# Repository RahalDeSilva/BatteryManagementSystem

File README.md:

# BatteryManagementSystem
EKF-based State of Charge estimator for Li-ion cells using NASA battery dataset

> ⚠️ Active development — ongoing BMS prototype. Expect breaking changes between commits.

A MATLAB-based Battery Management System (BMS) prototype focused on State of Charge (SOC) estimation for lithium-ion cells. Currently implements an Extended Kalman Filter (EKF) with a first-order RC equivalent circuit model, validated against a parallel Coulomb Counting benchmark using the NASA battery dataset.

---

## Current Status

| Module | Status |
|---|---|
| EKF SOC Estimator | ✅ In progress |
| Coulomb Counting benchmark | ✅ In progress |
| OCV–SOC lookup table | ✅ In progress |
| Cell balancing | 🔲 Planned |
| Thermal modelling | 🔲 Planned |
| State of Health (SOH) | 🔲 Planned |
| Embedded deployment | 🔲 Planned |

## Status (as of this checkpoint)
- ✅ EKF SOC estimation working on NASA 00001.csv (single discharge cycle)
- ✅ Variable timestep handling (9.4-13.9s)
- ✅ Current sign convention corrected (NASA: discharge = negative)
- ✅ Nonlinear OCV lookup table (extended range + densified knee region)
- 📊 Operational Voltage RMSE: 0.061 V (excludes end-of-discharge relaxation)
- 📌 Known limitation: residual spikes during end-of-discharge relaxation
  (1st-order RC model limitation — see Future Work)
- 📌 EKF vs Coulomb Counting gap (~3.4pp) likely due to placeholder
  capacity Q=2.0Ah vs actual aged-cell capacity — candidate for SOH module

---

## Battery Model

First-order RC equivalent circuit.

**State vector:** `x = [SOC, Vrc]`

**State equations:**

```
SOC(k+1) = SOC(k) − I·dt / Q
Vrc(k+1) = α·Vrc(k) + β·I

α = exp(−dt / (R1·C1))
β = R1·(1 − α)
```

**Terminal voltage measurement equation:**

```
V = OCV(SOC) − I·R0 − Vrc
```

---

## Repository Structure

```
BatteryManagementSystem/
├── SOC_Estimation/
    ├── data/
│       └── 00001.csv         % NASA Li-ion discharge dataset
│   ├── main.m            % EKF loop + Coulomb counting + plots
│   ├── battery_step.m    % RC circuit state transition function
│   ├── ekf_step.m        % EKF predict and update step
│   ├── ocv.m             % Nonlinear OCV piecewise-linear lookup
│   └── load_data.m       % NASA dataset loader
└── README.md
```

---

## Requirements

- MATLAB R2020a or later
- No additional toolboxes required for current modules

---

## Dataset

NASA battery discharge dataset (00001.csv).
Columns: `Voltage_measured`, `Current_measured`, `Temperature_measured`, `Current_load`, `Voltage_load`, `Time`

> Note: NASA dataset uses a non-standard current sign convention. Discharge current is negated in `load_data.m` before processing.

---

## EKF Tuning Parameters

| Parameter | Value | Description |
|---|---|---|
| Q | 2.0 Ah | Nominal cell capacity |
| R0 | ~0.05 Ω | Series resistance |
| R1 | ~0.02 Ω | RC branch resistance |
| C1 | ~2000 F | RC branch capacitance |
| Qk(1,1) | 1e-7 | Process noise — SOC |
| Qk(2,2) | 1e-5 | Process noise — Vrc |
| Rk | 4e-4 | Measurement noise (0.02V std) |

---

## References

- Gregory Plett, *Algorithms for Battery Management Systems* — Coursera
- NASA Prognostics Center of Excellence Battery Dataset
- Plett, G.L., *Battery Management Systems, Vol. 1: Battery Modeling*

---

## License

MIT License — see `LICENSE` for details.

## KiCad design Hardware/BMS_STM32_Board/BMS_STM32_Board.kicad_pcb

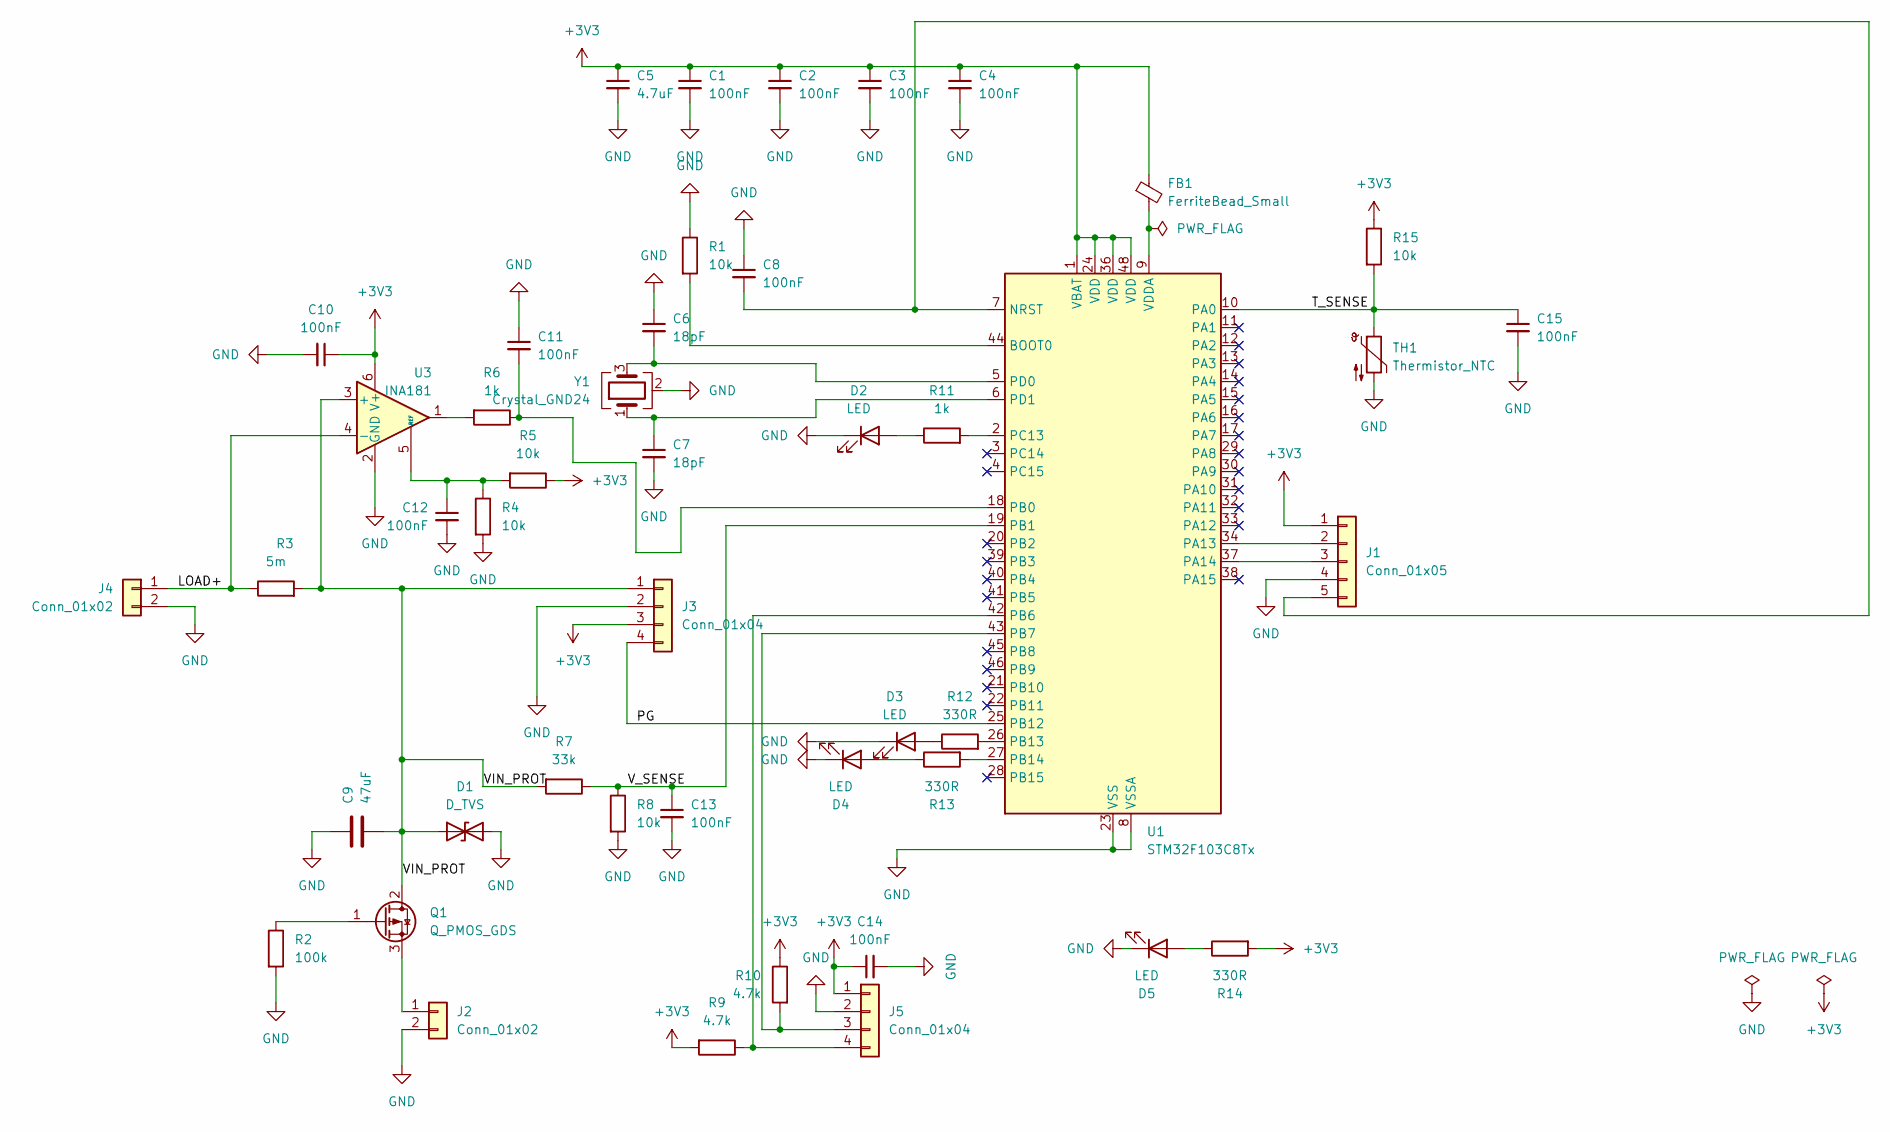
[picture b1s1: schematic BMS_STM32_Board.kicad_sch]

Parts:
C1, C2, C3, C4, C8, C10, C11, C12, C13, C14, C15: 100nF; C_0603_1608Metric
C5: 4.7uF; C_0805_2012Metric
C6, C7: 18pF; C_0603_1608Metric
C9: 47uF; CP_Radial_D6.3mm_P2.50mm
D1: D_TVS; D_SMA
D2, D3, D4, D5: LED; LED_0805_2012Metric
FB1: FerriteBead_Small; L_0603_1608Metric
J1: Conn_01x05; PinHeader_1x05_P2.54mm_Vertical
J2, J4: Conn_01x02; TerminalBlock_Phoenix_MKDS-3-2-5.08_1x02_P5.08mm_Horizontal
J3, J5: Conn_01x04; PinHeader_1x04_P2.54mm_Vertical
Q1: Q_PMOS_GDS; TO-252-3_TabPin2
R1, R4, R5, R8, R15: 10k; R_0603_1608Metric
R2: 100k; R_0603_1608Metric
R3: 5m; R_2512_6332Metric
R6, R11: 1k; R_0603_1608Metric
R7: 33k; R_0603_1608Metric
R9, R10: 4.7k; R_0603_1608Metric
R12, R13, R14: 330R; R_0603_1608Metric
TH1: Thermistor_NTC; PinHeader_1x02_P2.54mm_Vertical
U1: STM32F103C8Tx; LQFP-48_7x7mm_P0.5mm
U3: INA181; SOT-23-6
Y1: Crystal_GND24; Crystal_SMD_3225-4Pin_3.2x2.5mm

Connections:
+3V3: C1.1, C2.1, C3.1, C4.1, C5.1, C10.1, C14.1, FB1.1, J1.1, J3.3, J5.1, R5.1, R9.2, R10.1, R14.2, R15.1, U1.1 (VBAT), U1.24 (VDD), U1.36 (VDD), U1.48 (VDD), U3.6 (V+)
/LOAD+: J4.1, R3.1, U3.4 (-)
/PG: J3.4, U1.25 (PB12)
/T_SENSE: C15.1, R15.2, TH1.1, U1.10 (PA0)
/VIN_PROT: C9.2, D1.1 (A1), J3.1, Q1.2 (D), R3.2, R7.2, U3.3 (+)
/V_SENSE: C13.1, R7.1, R8.1, U1.19 (PB1)
GND: C1.2, C2.2, C3.2, C4.2, C5.2, C6.1, C7.2, C8.1, C9.1, C10.2, C11.1, C12.2, C13.2, C14.2, C15.2, D1.2 (A2), D2.1 (K), D3.1 (K), D4.1 (K), D5.1 (K), J1.4, J2.2, J3.2, J4.2, J5.2, R1.1, R2.2, R4.2, R8.2, TH1.2, U1.8 (VSSA), U1.23 (VSS), U1.35 (VSS), U1.47 (VSS), U3.2 (GND), Y1.2 (G), Y1.4 (G)
unnamed: D2.2 (A), R11.1
unnamed: D3.2 (A), R12.1
unnamed: D4.2 (A), R13.1
unnamed: D5.2 (A), R14.1
unnamed: J1.2, U1.34 (PA13)
unnamed: J1.3, U1.37 (PA14)
unnamed: C8.2, J1.5, U1.7 (NRST)
unnamed: J2.1, Q1.3 (S)
unnamed: J5.3, R10.2, U1.43 (PB7)
unnamed: J5.4, R9.1, U1.42 (PB6)
unnamed: Q1.1 (G), R2.1
unnamed: R6.2, U3.1
unnamed: R1.2, U1.44 (BOOT0)
unnamed: C11.2, R6.1, U1.18 (PB0)
unnamed: R12.2, U1.26 (PB13)
unnamed: R13.2, U1.27 (PB14)
unnamed: R11.2, U1.2 (PC13)
unnamed: C6.2, U1.5 (PD0), Y1.3
unnamed: C7.1, U1.6 (PD1), Y1.1
unnamed: FB1.2, U1.9 (VDDA)
unnamed: C12.1, R4.1, R5.2, U3.5 (REF)

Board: 2 copper layers, 46 parts (0 on the bottom side), 28 nets, no tracks yet.

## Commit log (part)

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2026-06-06 Initial commit: EKF SOC estimator with Coulomb counting benchmark
2026-06-11 debugging and folder change
2026-06-12 matlab simulation fixed
